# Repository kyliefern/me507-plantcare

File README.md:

# me507-plantcare

main.brd - Eagle board file

main.cpp - C++ source file

main.h - C++ header file

main.sch - Eagle schematic file

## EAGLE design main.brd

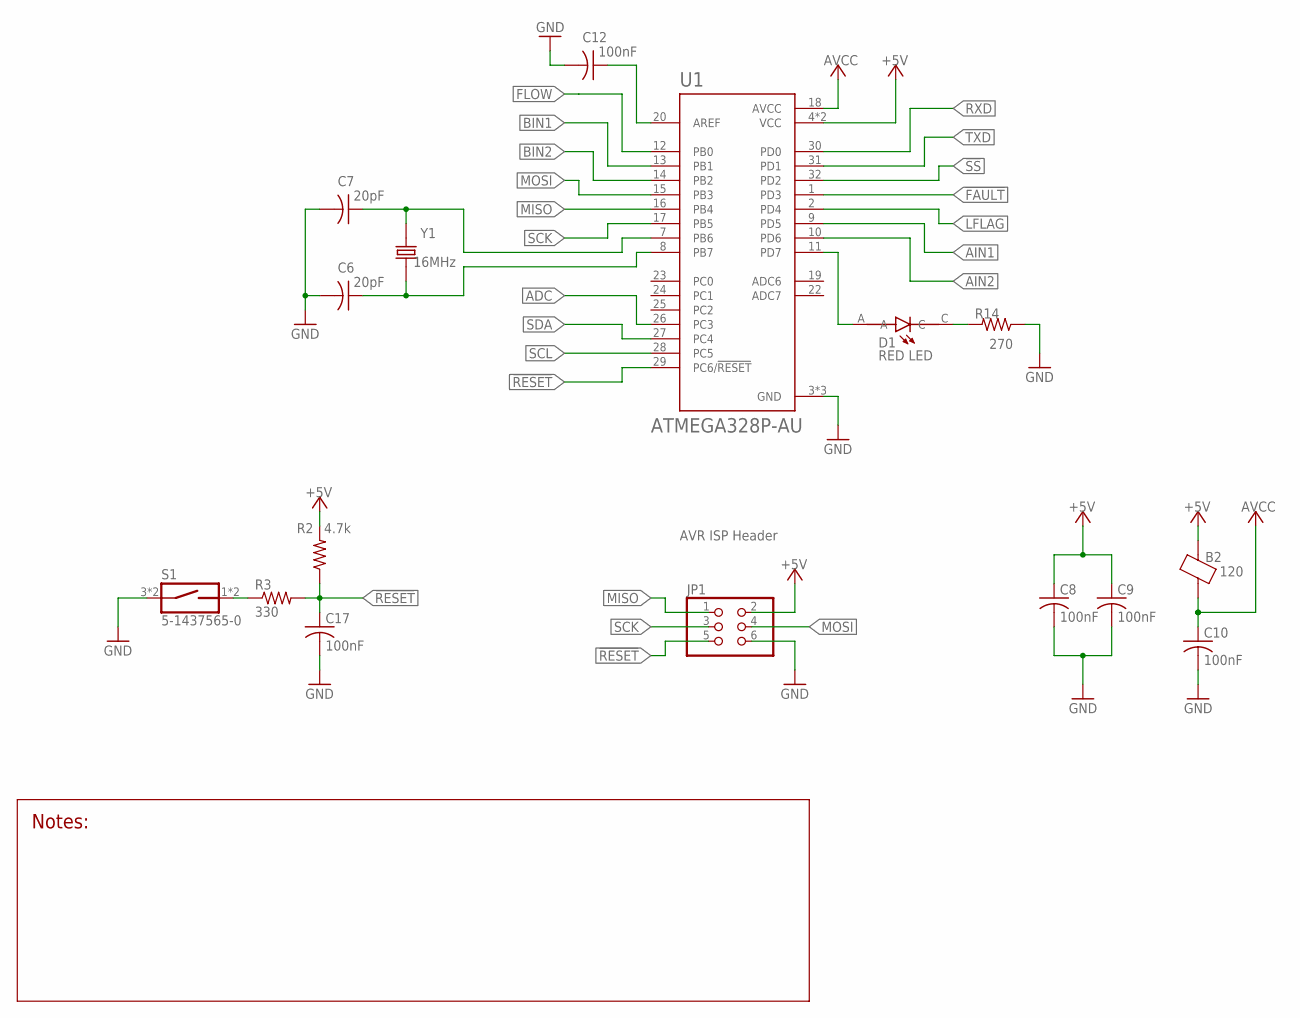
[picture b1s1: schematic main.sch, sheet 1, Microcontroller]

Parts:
B2: 120; 0805
C6, C7: 20pF; C0805
C8, C9, C10, C12, C17: 100nF; C0805
D1: RED LED; LEDM1608X80
JP1: PINHD-2X3; 2X03
R2: 4.7k; R0805
R3: 330; R0805
R14: 270; R0805
S1: 5-1437565-0; SW_5-1437565-0
U1: ATMEGA328P-AU; QFP80P900X900X120-32N
Y1: 16MHz; XTAL_ECS-160-20-3X-TR

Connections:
!FAULT!: U1.1 (PD3); also elsewhere on the board
!RESET!: C17.1, JP1.5, R2.1, R3.2, U1.29 (PC6/!RESET)
!SS!: U1.32 (PD2); also elsewhere on the board
+5V: B2.2, C8.1, C9.1, JP1.2, R2.2, U1.4 (VCC), U1.6 (VCC); also elsewhere on the board
ADC: U1.26 (PC3); also elsewhere on the board
AIN1: U1.9 (PD5); also elsewhere on the board
AIN2: U1.10 (PD6); also elsewhere on the board
AREF: C12.1, U1.20 (AREF)
AVCC: B2.1, C10.1, U1.18 (AVCC)
BIN1: U1.13 (PB1); also elsewhere on the board
BIN2: U1.14 (PB2); also elsewhere on the board
FLOW: U1.12 (PB0); also elsewhere on the board
GND: C6.2, C7.2, C8.2, C9.2, C10.2, C12.2, C17.2, JP1.6, R14.1, S1.3 (1), S1.4 (1), U1.3 (GND), U1.5 (GND), U1.21 (GND); also elsewhere on the board
LED: D1.C, R14.2
LFLAG: U1.2 (PD4); also elsewhere on the board
MISO: JP1.1, U1.16 (PB4); also elsewhere on the board
MOSI: JP1.4, U1.15 (PB3); also elsewhere on the board
PD7: D1.A, U1.11 (PD7)
RXD: U1.30 (PD0); also elsewhere on the board
SCK: JP1.3, U1.17 (PB5); also elsewhere on the board
SCL: U1.28 (PC5); also elsewhere on the board
SDA: U1.27 (PC4); also elsewhere on the board
SW: R3.1, S1.1 (2), S1.2
TOSC1: C7.1, U1.7 (PB6), Y1.2
TOSC2: C6.1, U1.8 (PB7), Y1.1
TXD: U1.31 (PD1); also elsewhere on the board

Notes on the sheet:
AVR ISP Header

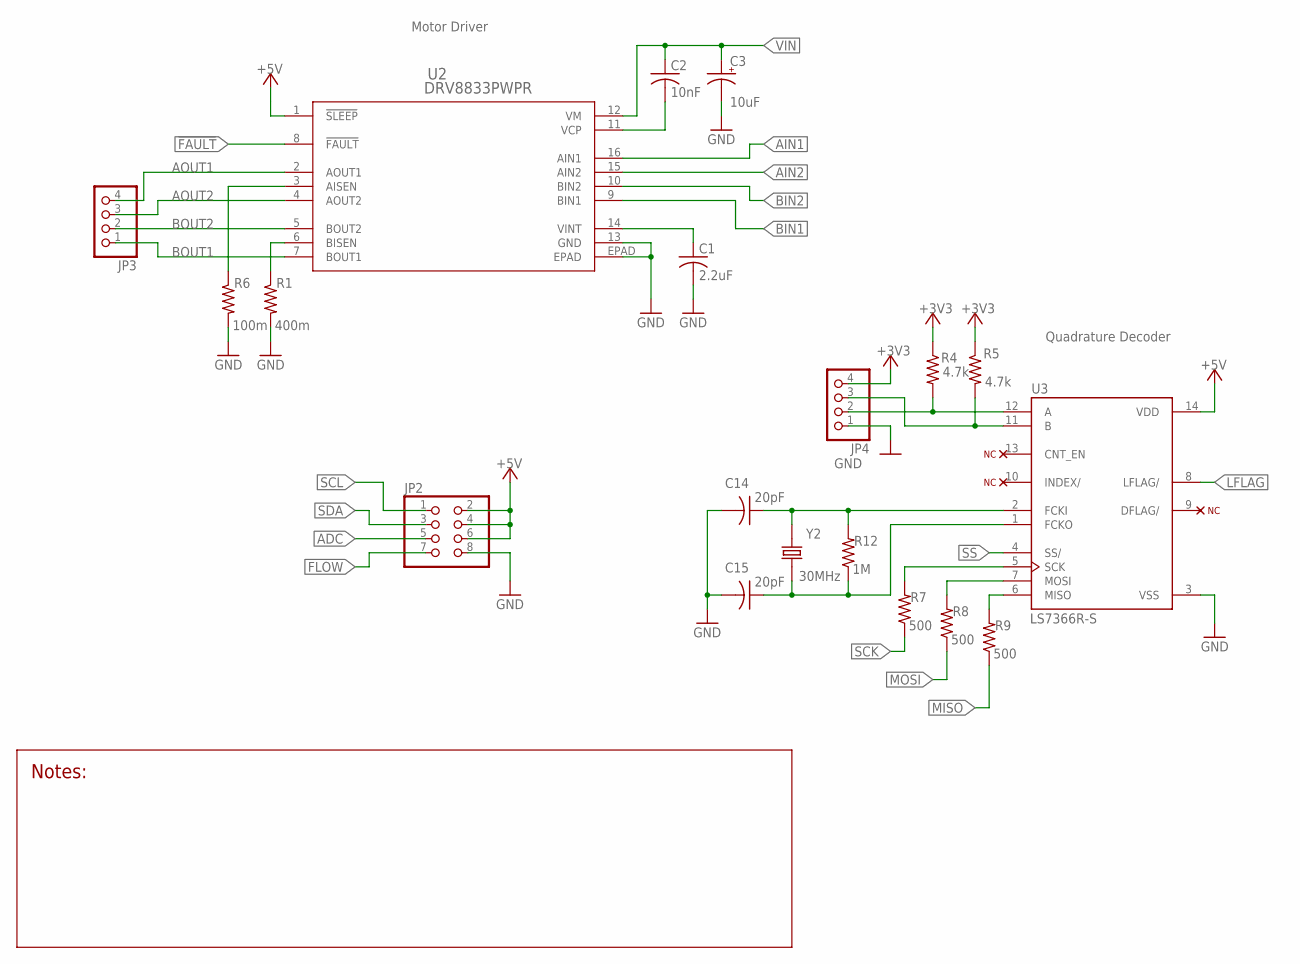
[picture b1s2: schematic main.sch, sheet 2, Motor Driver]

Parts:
C1: 2.2uF; C0805
C2: 10nF; C0805
C3: 10uF; E5-4
C14, C15: 20pF; C0805
JP2: PINHD-2X4; 2X04
JP3, JP4: PINHD-1X4; 1X04
R1: 400m; R0805
R4, R5: 4.7k; R0805
R6: 100m; R0805
R7, R8, R9: 500; R0805
R12: 1M; R0805
U2: DRV8833PWPR; PWP16_2P31X2P46
U3: LS7366R-S; SOIC127P600X175-14N
Y2: 30MHz; XTAL_ECS-160-20-3X-TR

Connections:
!FAULT!: U2.8 (!FAULT!); also elsewhere on the board
!SS!: U3.4 (SS/); also elsewhere on the board
+3V3: JP4.4, R4.1, R5.1; also elsewhere on the board
+5V: JP2.2, JP2.4, JP2.6, U2.1 (!SLEEP!), U3.14 (VDD); also elsewhere on the board
ADC: JP2.5; also elsewhere on the board
AIN1: U2.16 (AIN1); also elsewhere on the board
AIN2: U2.15 (AIN2); also elsewhere on the board
AISEN: R6.1, U2.3 (AISEN)
AOUT1: JP3.4, U2.2 (AOUT1)
AOUT2: JP3.3, U2.4 (AOUT2)
BIN1: U2.9 (BIN1); also elsewhere on the board
BIN2: U2.10 (BIN2); also elsewhere on the board
BISEN: R1.1, U2.6 (BISEN)
BOUT1: JP3.1, U2.7 (BOUT1)
BOUT2: JP3.2, U2.5 (BOUT2)
ENCA: JP4.2, R4.2, U3.12 (A)
ENCB: JP4.3, R5.2, U3.11 (B)
FCKI: C14.1, R12.2, U3.2 (FCKI), Y2.1
FCKO: C15.1, R12.1, U3.1 (FCKO), Y2.2
FLOW: JP2.7; also elsewhere on the board
GND: C1.2, C3.-, C14.2, C15.2, JP2.8, JP4.1, R1.2, R6.2, U2.13 (GND), U2.EPAD, U3.3 (VSS); also elsewhere on the board
LFLAG: U3.8 (LFLAG/); also elsewhere on the board
MI: R9.2, U3.6 (MISO)
MISO: R9.1; also elsewhere on the board
MO: R8.2, U3.7 (MOSI)
MOSI: R8.1; also elsewhere on the board
SCK: R7.1; also elsewhere on the board
SCL: JP2.1; also elsewhere on the board
SCLK: R7.2, U3.5 (SCK)
SDA: JP2.3; also elsewhere on the board
VCP: C2.2, U2.11 (VCP)
VIN: C2.1, C3.+, U2.12 (VM); also elsewhere on the board
VINT: C1.1, U2.14 (VINT)

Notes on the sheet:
Quadrature Decoder
Motor Driver

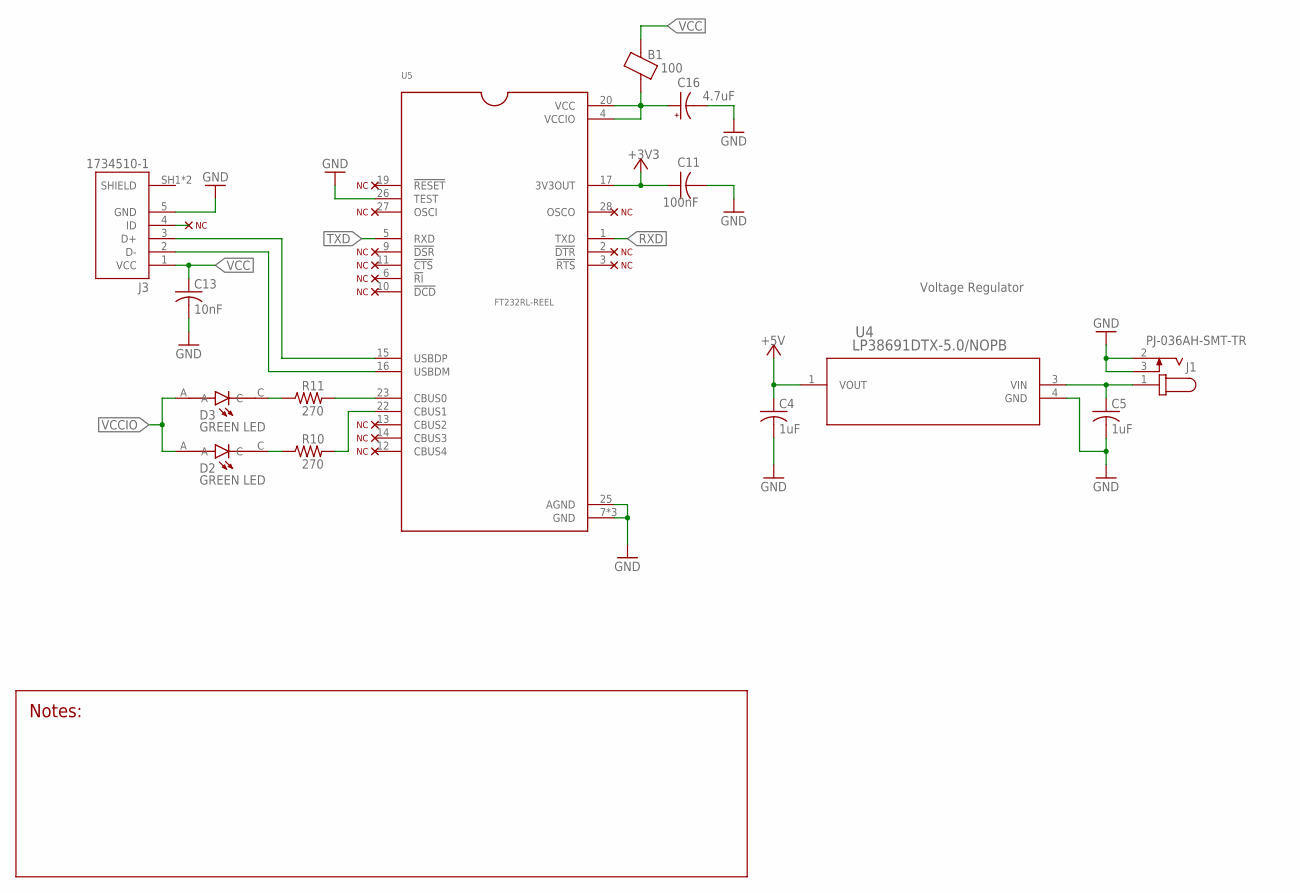
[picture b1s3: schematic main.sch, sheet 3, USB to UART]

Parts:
B1: 100; 0805
C4, C5: 1uF; C0805
C11: 100nF; C0805
C13: 10nF; C0805
C16: 4.7uF; E5-5
D2, D3: GREEN LED; LEDM1608X80
J1: PJ-036AH-SMT-TR; CUI_PJ-036AH-SMT-TR
J3: 1734510-1; TE_1734510-1
R10, R11: 270; R0805
U4: LP38691DTX-5.0/NOPB; TD03B
U5: FT232RL-REEL; SOP65P780X200-28N

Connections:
+3V3: C11.1, U5.17 (3V3OUT); also elsewhere on the board
+5V: C4.1, U4.1 (VOUT); also elsewhere on the board
BUS0: R11.2, U5.23 (CBUS0)
BUS1: R10.2, U5.22 (CBUS1)
DM: J3.2 (D-), U5.16 (USBDM)
DP: J3.3 (D+), U5.15 (USBDP)
GND: C4.2, C5.2, C11.2, C13.2, C16.-, J1.2, J1.3, J3.5 (GND), U4.4 (GND), U5.7 (GND), U5.18 (GND), U5.21 (GND), U5.25 (AGND), U5.26 (TEST); also elsewhere on the board
RXD: U5.1 (TXD); also elsewhere on the board
RXLED: D2.C, R10.1
TXD: U5.5 (RXD); also elsewhere on the board
TXLED: D3.C, R11.1
VCC: B1.2, C13.1, J3.1 (VCC)
VCCIO: B1.1, C16.+, D2.A, D3.A, U5.4 (VCCIO), U5.20 (VCC)
VIN: C5.1, J1.1, U4.3 (VIN); also elsewhere on the board

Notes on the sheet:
Voltage Regulator

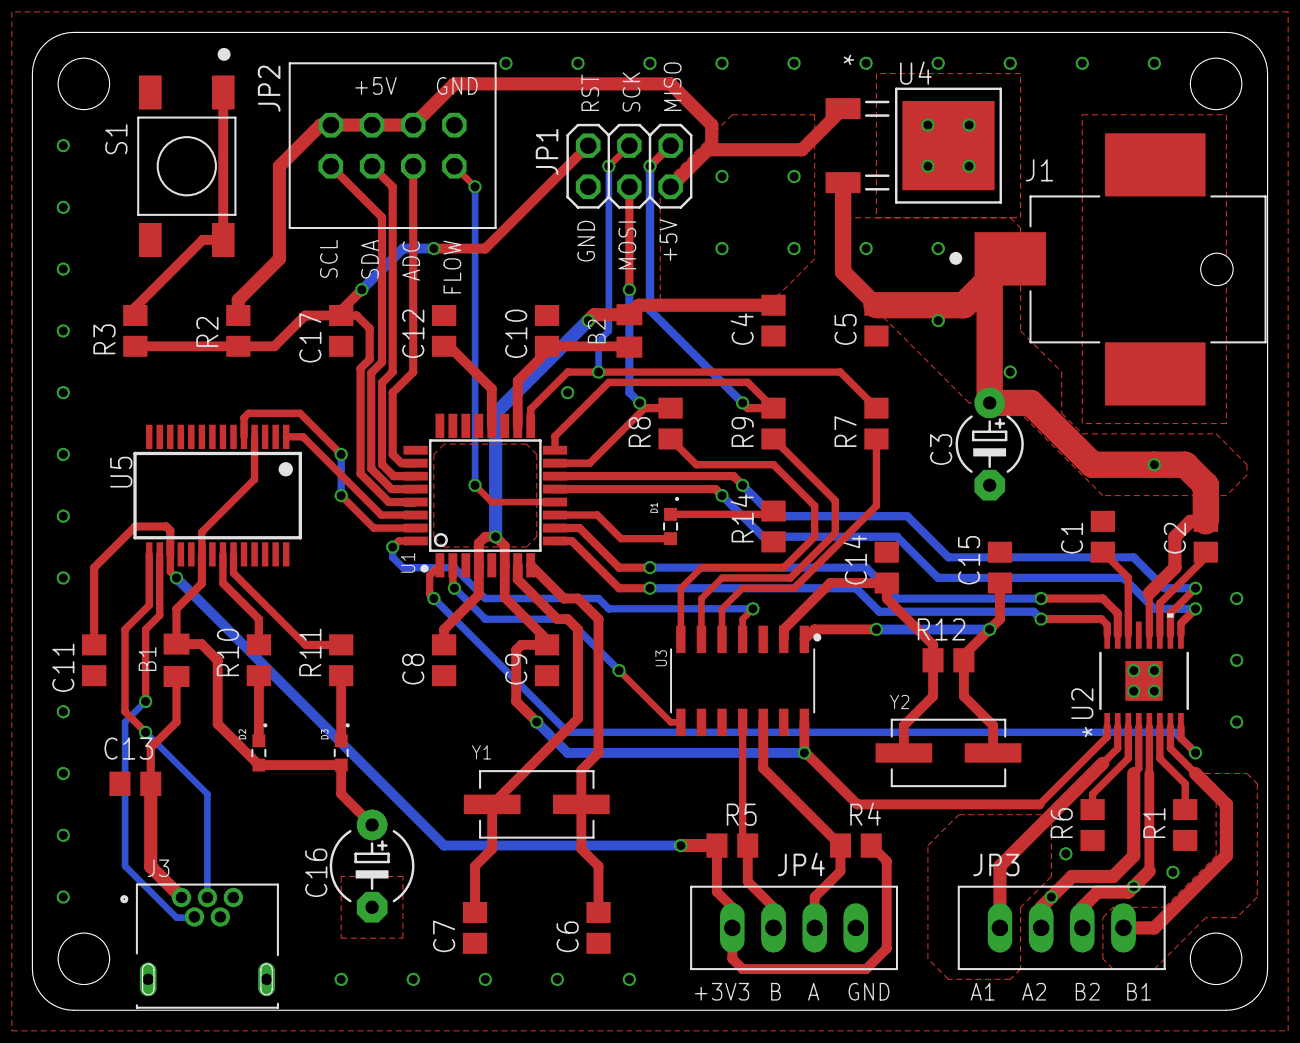
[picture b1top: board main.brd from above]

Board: 2 copper layers, 76.2 x 60.3 mm, 49 parts (0 on the bottom side), 51 nets.
